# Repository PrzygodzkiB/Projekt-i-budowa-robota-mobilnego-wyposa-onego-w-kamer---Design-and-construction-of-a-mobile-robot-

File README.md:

# Design and construction of a mobile robot 
## English
This engineering thesis is written in Polish. However, if someone wants to see the code for ESP 32 CAM microcontrollers for transmitting the image from the camera and ESP 32 for controlling the control via wifi, you are welcome. 

The work presents the construction process and implementation of a mobile robot software
equipped with a camera. Its assumption is to construct a remotely controlled unit enabling
smooth image transmission. The scope of work is also related to the commissioning and testing
of the constructed structure.

The completed vehicle was designed to work well at home. It was with this in mind that
the engines and the platform were selected. During the design stage, it was decided to use
two microcontrollers, due to the limitations of one of them and the desire to liquefy the
camera image. The method of selecting a driver for motors, sonars, power source and voltage
stabilizer has also been described. When designing the electronic part, care was taken to ensure
the appropriate temperature of the system and safety in the event of short circuits. Schematic
diagrams and block diagrams of electrical connections in the system are also presented. There
is also a description of two hand-designed PCBs.

As part of the work, the robot successfully communicated with the user via wi-fi. A website
was also written to serve as a driving control panel. It contains the image from the robot’s
camera as well as the results of distance and voltage measurements. UART’s communications
were also used to pass commands between the microcontrollers.

In order to drive the robot in a straight line, three methods of regulation were compared.
They were made on the basis of PI regulators, which synchronized the work of the engines or
did not do it. There are also written anti-collision functions while driving based on distance
measurements made with the use of sonars.
## Polish

Praca przedstawia proces budowy oraz implementację oprogramowania robota mobilnego
wyposażonego w kamerę. Jej założeniem jest skonstruowanie zdalnie sterowanej jednostki
umożliwiającej płynne przekazywanie obrazu. Zakres pracy wiąże się również z uruchomieniem
i przetestowaniem wykonanej konstrukcji.

Analizując tematykę zagadnienia, dokonano zestawienia trzech robotów z kamerą. Do
tego celu wybrano konstrukcje o zróżnicowanej budowie oraz przeznaczeniu. Z ich opisów
zaczerpnięto zastosowania później wykorzystane we własnym robocie.

Wykonany pojazd został zaprojektowany tak, aby sprawdzał się w warunkach domowych.
Pod tym kątem dokonano wyboru silników oraz platformy. W czasie projektowania zdecydowano
się na użycie dwóch mikrokontrolerów, z powodów ograniczeń jednego z nich oraz
z chęci upłynnienia obrazu kamery. Dokonano również opisu sposobu doboru sterownika
silników, sonarów, źródła zasilania oraz stabilizatora napięcia. Projektując część elektroniczną,
zadbano o odpowiednią temperaturę układu oraz o bezpieczeństwo w przypadku wystąpienia
zwarć. Przedstawiono też schematy ideowe oraz blokowe połączeń elektrycznych w układzie.
Umieszczono również opis dwóch własnoręcznie zaprojektowanych płytek PCB.

W ramach pracy dokonano udanej komunikacji robota z użytkownikiem za pomocą wi-fi.
Napisano również stronę internetową służącą jako panel kontroli jazdy. Witryna wyświetla obraz
z kamery robota oraz wyniki pomiarów odległości i napięcia. Zastosowano również komunikacje
UART w celu przekazywania poleceń między mikrokontrolerami.

Aby zrealizować jazdę robota po linii prostej, dokonano porównania trzech sposobów
regulacji. Były one zrealizowane na postawie regulatorów PI, które synchronizowały prace
silników lub tego nie robiły. Napisano również funkcje zabezpieczające przed kolizją w czasie
jazdy na podstawie pomiarów odległości wykonywanych za pomocą sonarów.

W czasie testów dokonano oceny otrzymywanego obrazu. Okazał on się płynny i wyraźny
na tyle, by zidentyfikować co, znajduje się w otoczeniu robota. Za pomocą wyników testu
jazdy po linii prostej wykonano zestawienie osiągnięć różnych sposobów sterowania. Udało
się dzięki temu wytypować najlepszy z nich. Dokonano również sprawdzenia bezkolizyjności
robota. Zastosowane sonary okazały się wystarczające, jednak znaleziono też wady użytego
zastosowania. Można uznać, że całościowy projekt sprawdził się w swoim przeznaczeniu.

## Pictures

Website to communicate with robot

Robot

Feel free to use

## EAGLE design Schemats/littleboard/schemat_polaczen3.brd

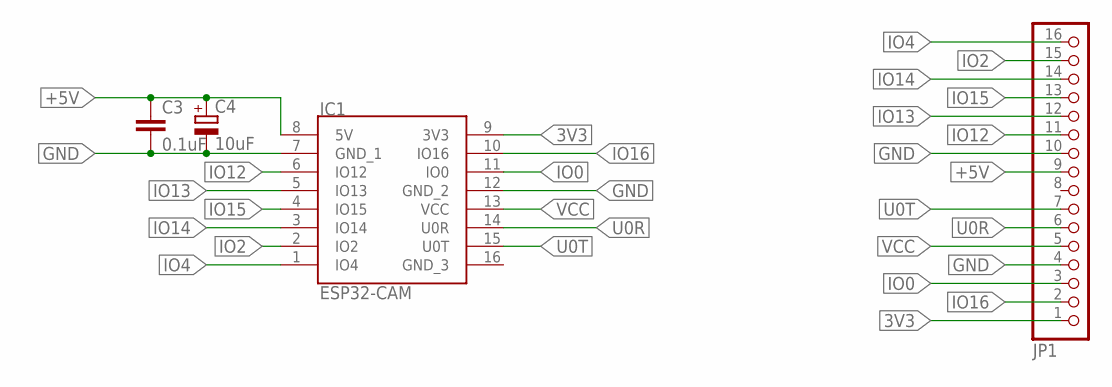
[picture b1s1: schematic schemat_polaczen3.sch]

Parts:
C3: 0.1uF; C025-024X044
C4: 10uF; E2,5-6E
IC1: ESP32-CAM; ESP32CAM
JP1: PINHD-1X16/90; 1X16/90

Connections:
3V3: IC1.9 (3V3), JP1.1
+5V: C3.1, C4.+, IC1.8 (5V), JP1.9
GND: C3.2, C4.-, IC1.7 (GND_1), IC1.12 (GND_2), JP1.4, JP1.10
IO0: IC1.11 (IO0), JP1.3
IO2: IC1.2 (IO2), JP1.15
IO4: IC1.1 (IO4), JP1.16
IO12: IC1.6 (IO12), JP1.11
IO13: IC1.5 (IO13), JP1.12
IO14: IC1.3 (IO14), JP1.14
IO15: IC1.4 (IO15), JP1.13
IO16: IC1.10 (IO16), JP1.2
U0R: IC1.14 (U0R), JP1.6
U0T: IC1.15 (U0T), JP1.7
VCC: IC1.13 (VCC), JP1.5

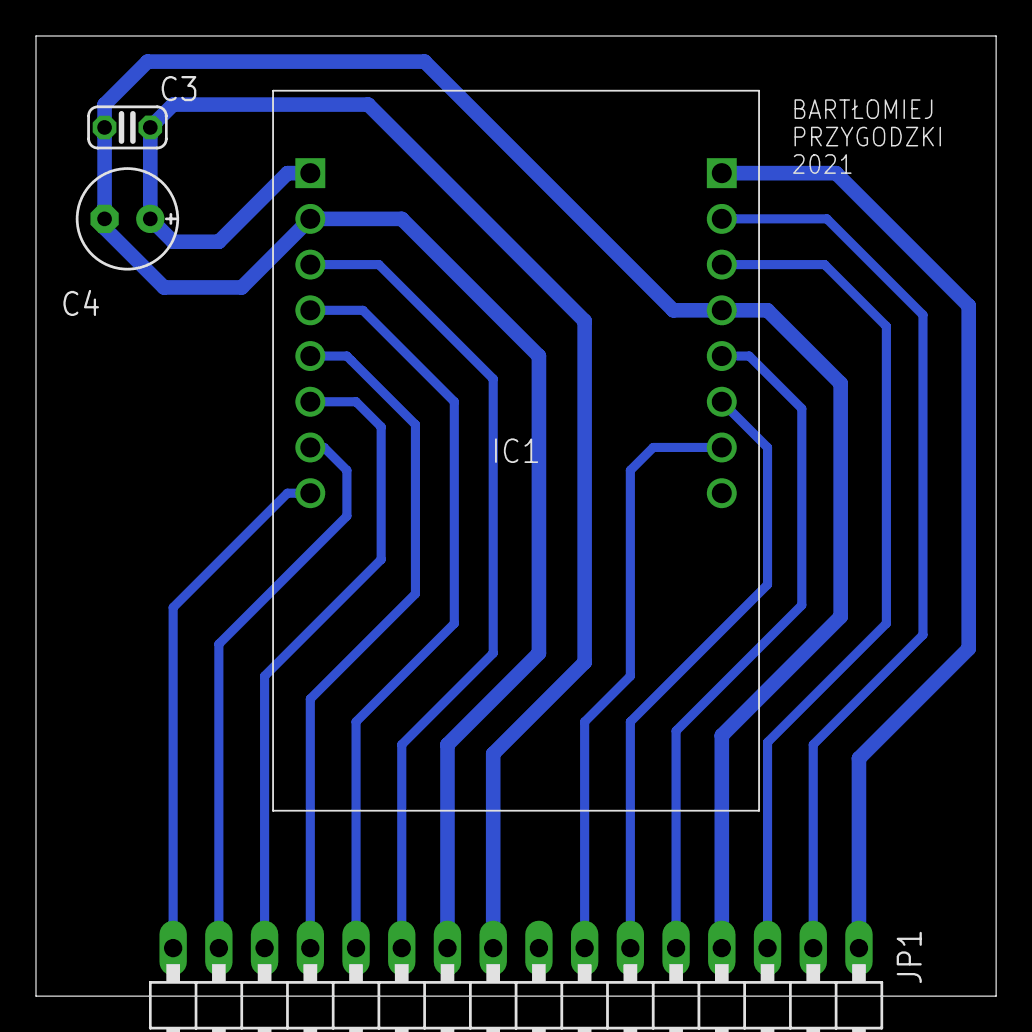
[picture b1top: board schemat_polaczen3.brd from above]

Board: 2 copper layers, 53.3 x 53.3 mm, 4 parts (0 on the bottom side), 14 nets.

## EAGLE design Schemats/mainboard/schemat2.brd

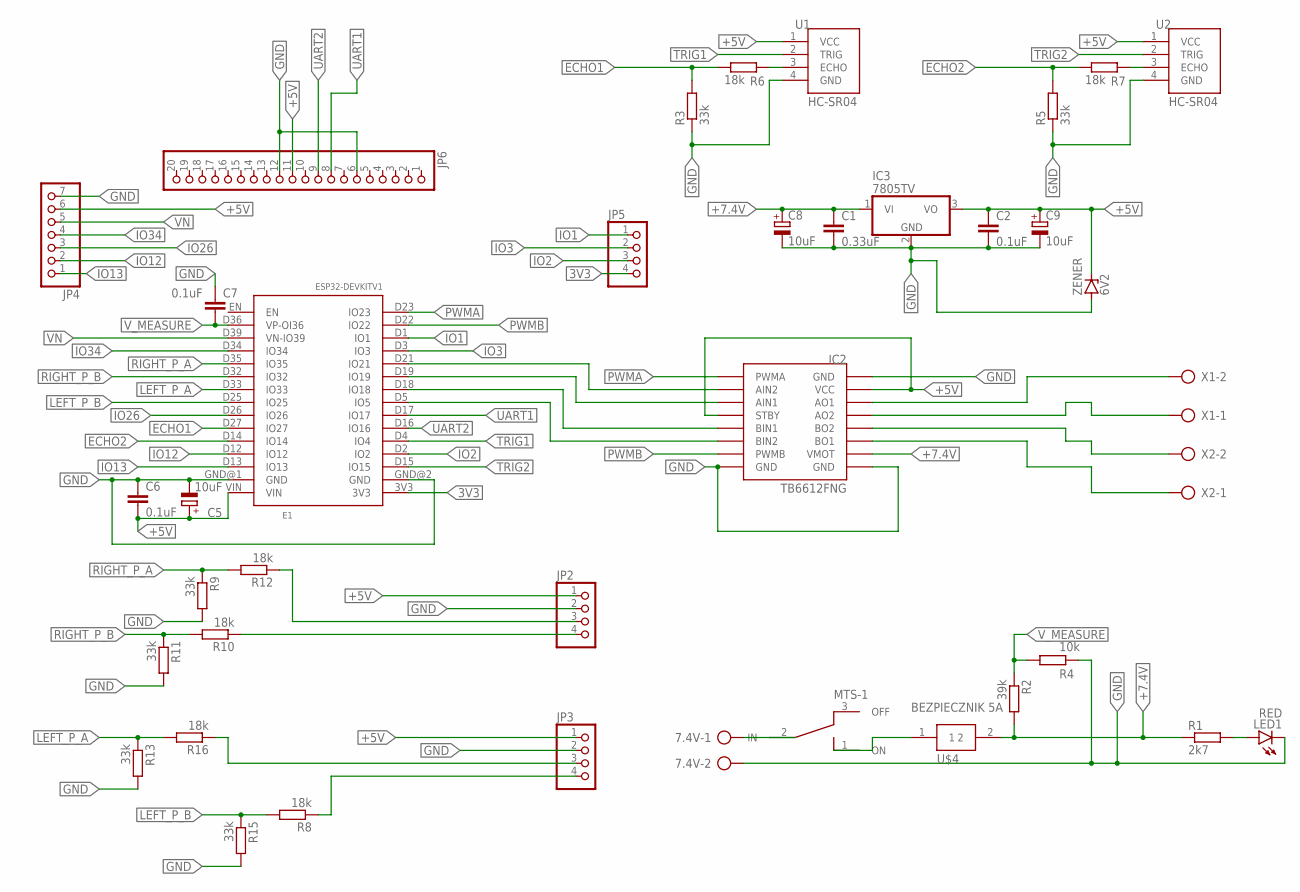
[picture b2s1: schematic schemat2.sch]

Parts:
7.4V: AK500/2
C1: 0.33uF; C025-024X044
C2, C6, C7: 0.1uF; C025-024X044
C5, C8, C9: 10uF; E2,5-6E
E1: ESP32DEVKITV1; ESP32-DEVKITV1
IC2: MODUL_POLOLU
IC3: 7805TV; TO220V
JP2, JP3, JP5: PINHD-1X4; 1X04
JP4: PINHD-1X7; 1X07
JP6: PINHD-1X20; 1X20
LED1: RED; LED5MM
R1: 2k7; 0207/5V
R2: 39k; 0207/5V
R3, R5, R9, R11, R13, R15: 33k; 0207/5V
R4: 10k; 0207/5V
R6, R7, R8, R10, R12, R16: 18k; 0207/5V
U1, U2: HC-SR04; XCVR_HC-SR04
U$1: MTS-1; SWITCH_TOGGLE
U$4: BEZPIECZNIK 5A; BEZPIECZNIK_GNIAZDO
X1, X2: AK500/2
ZENER: 6V2; DO35Z10

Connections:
3V3: E1.3V3, JP5.4
+5V: C2.1, C5.+, C6.2, C9.+, E1.VIN, IC2.STBY, IC2.VCC, IC3.3 (VO), JP2.1, JP3.1, JP4.6, JP6.11, U1.1 (VCC), U2.1 (VCC), ZENER.C
+7.4V: C1.1, C8.+, IC2.VMOT, IC3.1 (VI), R1.1, R2.2, U$4.2
A: JP3.3, R16.1
A1: JP2.3, R12.1
B: JP3.4, R8.1
B1: JP2.4, R10.1
ECHO1: E1.D27 (IO27), R3.2, R6.1
ECHO2: E1.D14 (IO14), R5.2, R7.1
GND: 7.4V.2, C1.2, C2.2, C5.-, C6.1, C7.1, C8.-, C9.-, E1.GND@1 (GND), E1.GND@2 (GND), IC2.GND1 (GND), IC2.GND2 (GND), IC2.GND3 (GND), IC3.2 (GND), JP2.2, JP3.2, JP4.7, JP6.6, JP6.12, LED1.K (C), R3.1, R4.2, R5.1, R9.2, R11.2, R13.2, R15.2, U1.4 (GND), U2.4 (GND), ZENER.A
IO1: E1.D1 (IO1), JP5.1
IO2: E1.D2 (IO2), JP5.3
IO3: E1.D3 (IO3), JP5.2
IO12: E1.D12 (IO12), JP4.2
IO13: E1.D13 (IO13), JP4.1
IO26: E1.D26 (IO26), JP4.3
IO34: E1.D34 (IO34), JP4.4
LEFT_P_A: E1.D33 (IO33), R13.1, R16.2
LEFT_P_B: E1.D25 (IO25), R8.2, R15.1
L_MOT+: IC2.BO2, X2.2
L_MOT-: IC2.BO1, X2.1
unnamed: LED1.A, R1.2
unnamed: R6.2, U1.3 (ECHO)
unnamed: R7.2, U2.3 (ECHO)
unnamed: 7.4V.1, U$1.2 (IN)
unnamed: E1.D5 (IO5), IC2.BIN2
unnamed: E1.D18 (IO18), IC2.BIN1
unnamed: E1.D21 (IO21), IC2.AIN2
unnamed: E1.D19 (IO19), IC2.AIN1
unnamed: U$1.1 (ON), U$4.1
PWMA: E1.D23 (IO23), IC2.PWMA
PWMB: E1.D22 (IO22), IC2.PWMB
RIGHT_P_A: E1.D35 (IO35), R9.1, R12.2
RIGHT_P_B: E1.D32 (IO32), R10.2, R11.1
R_MOT+: IC2.AO1, X1.2
R_MOT-: IC2.A02 (AO2), X1.1
TRIG1: E1.D4 (IO4), U1.2 (TRIG)
TRIG2: E1.D15 (IO15), U2.2 (TRIG)
UART1: E1.D17 (IO17), JP6.8
UART2: E1.D16 (IO16), JP6.9
VN: E1.D39 (VN-IO39), JP4.5
V_MEASURE: C7.2, E1.D36 (VP-OI36), R2.1, R4.1

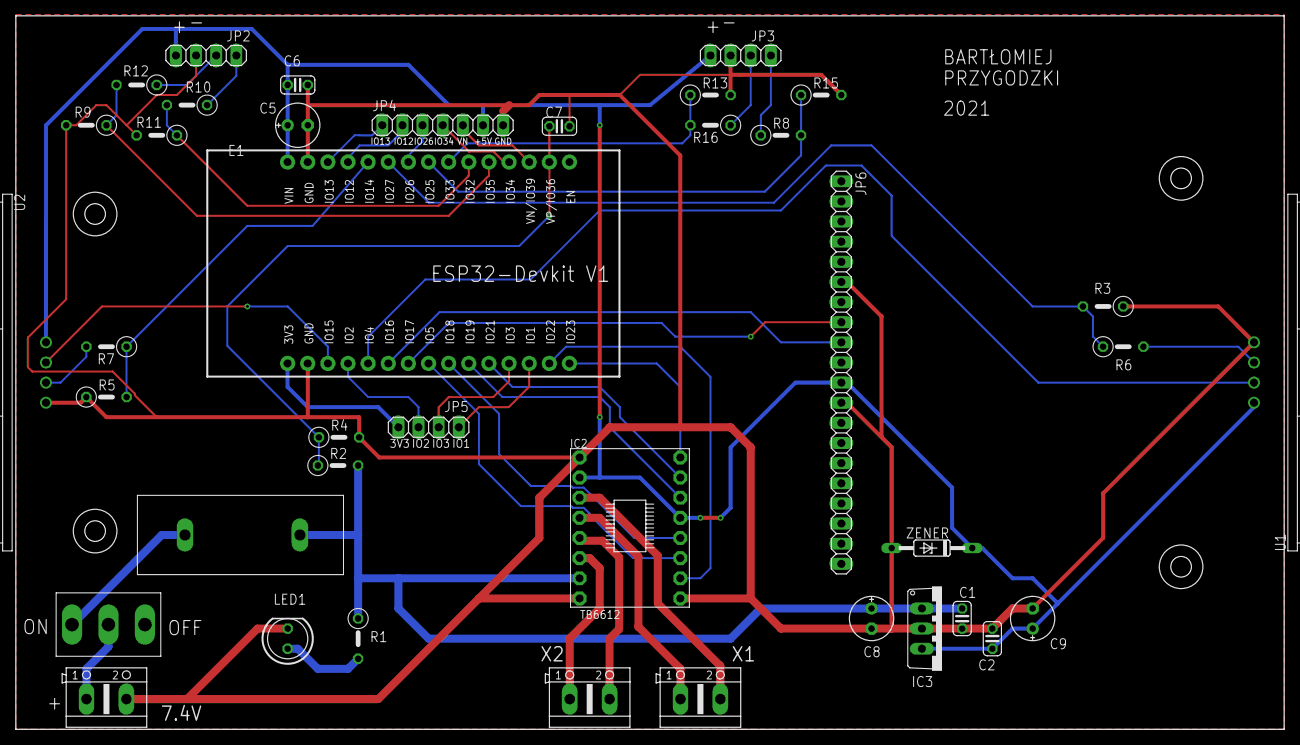
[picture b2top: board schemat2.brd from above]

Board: 2 copper layers, 160.0 x 90.0 mm, 39 parts (0 on the bottom side), 42 nets.
